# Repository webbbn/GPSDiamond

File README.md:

# GSPDiamond
Hardware design and firmware for a GPS based on the u-blox SAM-M8Q module.

## Configure/compile ChibiOS

### Download and unpack ChibiOS

`wget` https://osdn.net/dl/chibios/ChibiOS_19.1.1.7z
`7z x ChibiOS_19.1.1.7z`

### Download and install the ARM compiler

https://developer.arm.com/tools-and-software/open-source-software/developer-tools/gnu-toolchain/gnu-rm/downloads

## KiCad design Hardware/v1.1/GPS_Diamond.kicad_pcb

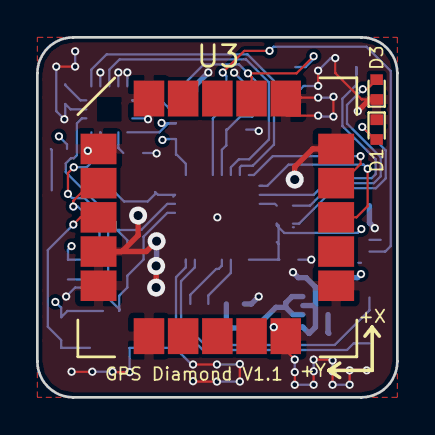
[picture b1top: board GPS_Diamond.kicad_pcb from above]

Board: 4 copper layers, 20.0 x 20.0 mm, 38 parts (0 on the bottom side), 24 nets.

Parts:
B1: SW_Push; SW_SPST_B3U-1000P
B2: SW_Push; SW_SPST_B3U-3000P
BT1: Battery_Cell; CPH3225A
C1, C5, C6, C8, C10, C12, C13, C14, C15: 100nF; C_0402
C2, C7, C9: 4.7uF; C_0402
C3, C16: 1uF; C_0402
C4: 10nF; C_0402
C11: 100nF; C_0402_NoSilk
D1, D3: LED; LED_0402
D2: D; D_0603
J1: CONN_01X04_MALE; JST_SH_SM04B-SRSS-TB_04x1.00mm_Angled
J2, J3, J5, J6: TEST_1P; Measurement_Point_Square-SMD-Pad_Small
R1: 510R; R_0402
R3, R4: 100R; R_0402
R6: 2k2; R_0402
R7: 10k; R_0402
R8: 2K2; R_0402
U1: MIC5353-3.3YMT-TR; MIC-5353
U2: STM32F042K6Ux; UFQFPN32
U3: SAM-M8Q
U4: FXOS8700CQ
U5: MS5637

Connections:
+3V3: B2.2, C2.1, C3.1, C4.1, C6.1, C7.1, C8.1, C9.1, C10.1, C11.1, C13.1, C14.1, D2.2, R1.1, R3.2, R6.2, R8.2, U1.4, U2.1, U2.5, U2.17, U3.2, U3.17, U4.1, U4.14, U5.1
+5V: C16.1, J1.2, U1.1, U1.3
+BATT: BT1.1, D2.1, U3.3
GND: BT1.2, C1.2, C2.2, C3.2, C4.2, C5.2, C6.2, C7.2, C8.2, C9.2, C10.2, C11.2, C12.2, C13.2, C14.2, C15.1, C16.2, D1.1, D3.1, J1.1, J3.1, R7.2, U1.2, U1.7, U2.33, U3.1, U3.4, U3.5, U3.6, U3.10, U3.11, U3.15, U3.16, U3.20, U4.3, U4.5, U4.7, U4.10, U4.12, U4.13, U4.16, U5.4
I2C1_SCL: R6.1, U2.29, U4.4, U5.3
I2C1_SDA: R8.1, U2.30, U4.6, U5.2
IMU_INT1: U2.6, U4.11
IMU_INT2: U2.7, U4.9
LED: R4.2, U2.11
unnamed: B1.1, R1.2
unnamed: B1.2, R7.1, U2.31
unnamed: B2.1, U2.10
unnamed: C1.1, U4.8
unnamed: C5.1, U1.6
unnamed: C12.1, U4.2
unnamed: C15.2, J2.1, U2.4
unnamed: D1.2, R3.1
unnamed: D3.2, R4.1
unnamed: J5.1, U2.23
unnamed: J6.1, U2.24
USART1_RX: J1.4, U2.20
USART1_TX: J1.3, U2.19
USART2_RX: U2.9, U3.13
USART2_TX: U2.8, U3.14

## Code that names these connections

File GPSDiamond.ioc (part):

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Mcu.Name=STM32F042K(4-6)Tx
Mcu.Package=LQFP32
Mcu.UserName=STM32F042K6Tx
PA0.GPIOParameters=GPIO_PuPd,GPIO_Label
PA0.GPIO_Label=IMU_INT1
PA0.GPIO_PuPd=GPIO_PULLDOWN
PA0.Signal=GPIO_Input
PA1.GPIOParameters=GPIO_PuPd,GPIO_Label
PA1.GPIO_Label=IMU_INT2
PA1.GPIO_PuPd=GPIO_PULLDOWN
PA1.Signal=GPIO_Input
PA10.Mode=Asynchronous
PA10.Signal=USART1_RX
PA13.Mode=Serial_Wire
PA13.Signal=SYS_SWDIO
PA14.Mode=Serial_Wire
PA14.Signal=SYS_SWCLK
PA2.Mode=Asynchronous
PA2.Signal=USART2_TX
PA3.Mode=Asynchronous
PA3.Signal=USART2_RX
PA5.GPIOParameters=GPIO_PuPd,GPIO_Label
PA5.GPIO_Label=LED
PA5.GPIO_PuPd=GPIO_PULLDOWN
PA5.Signal=GPIO_Output
PA9.Mode=Asynchronous
PA9.Signal=USART1_TX
PB6.Mode=I2C
PB6.Signal=I2C1_SCL
PB7.Mode=I2C
PB7.Signal=I2C1_SDA
RCC.SYSCLKFreq_VALUE=48000000
RCC.SYSCLKSource=RCC_SYSCLKSOURCE_PLLCLK
board=custom

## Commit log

2019-04-04 Initial commit of STM32 HAL-based firmware for the GPSDiamond.
2019-04-20 Working ms5637 driver.
2019-04-20 Adds Srs/syscall.c
2019-04-20 Moves the (incomplete) CubeMX version of the firmware to the CubeMX directory and adds the initial ChibiOS version, which is minimally working.
2019-04-20 Adds the v1.1 hardware files.
